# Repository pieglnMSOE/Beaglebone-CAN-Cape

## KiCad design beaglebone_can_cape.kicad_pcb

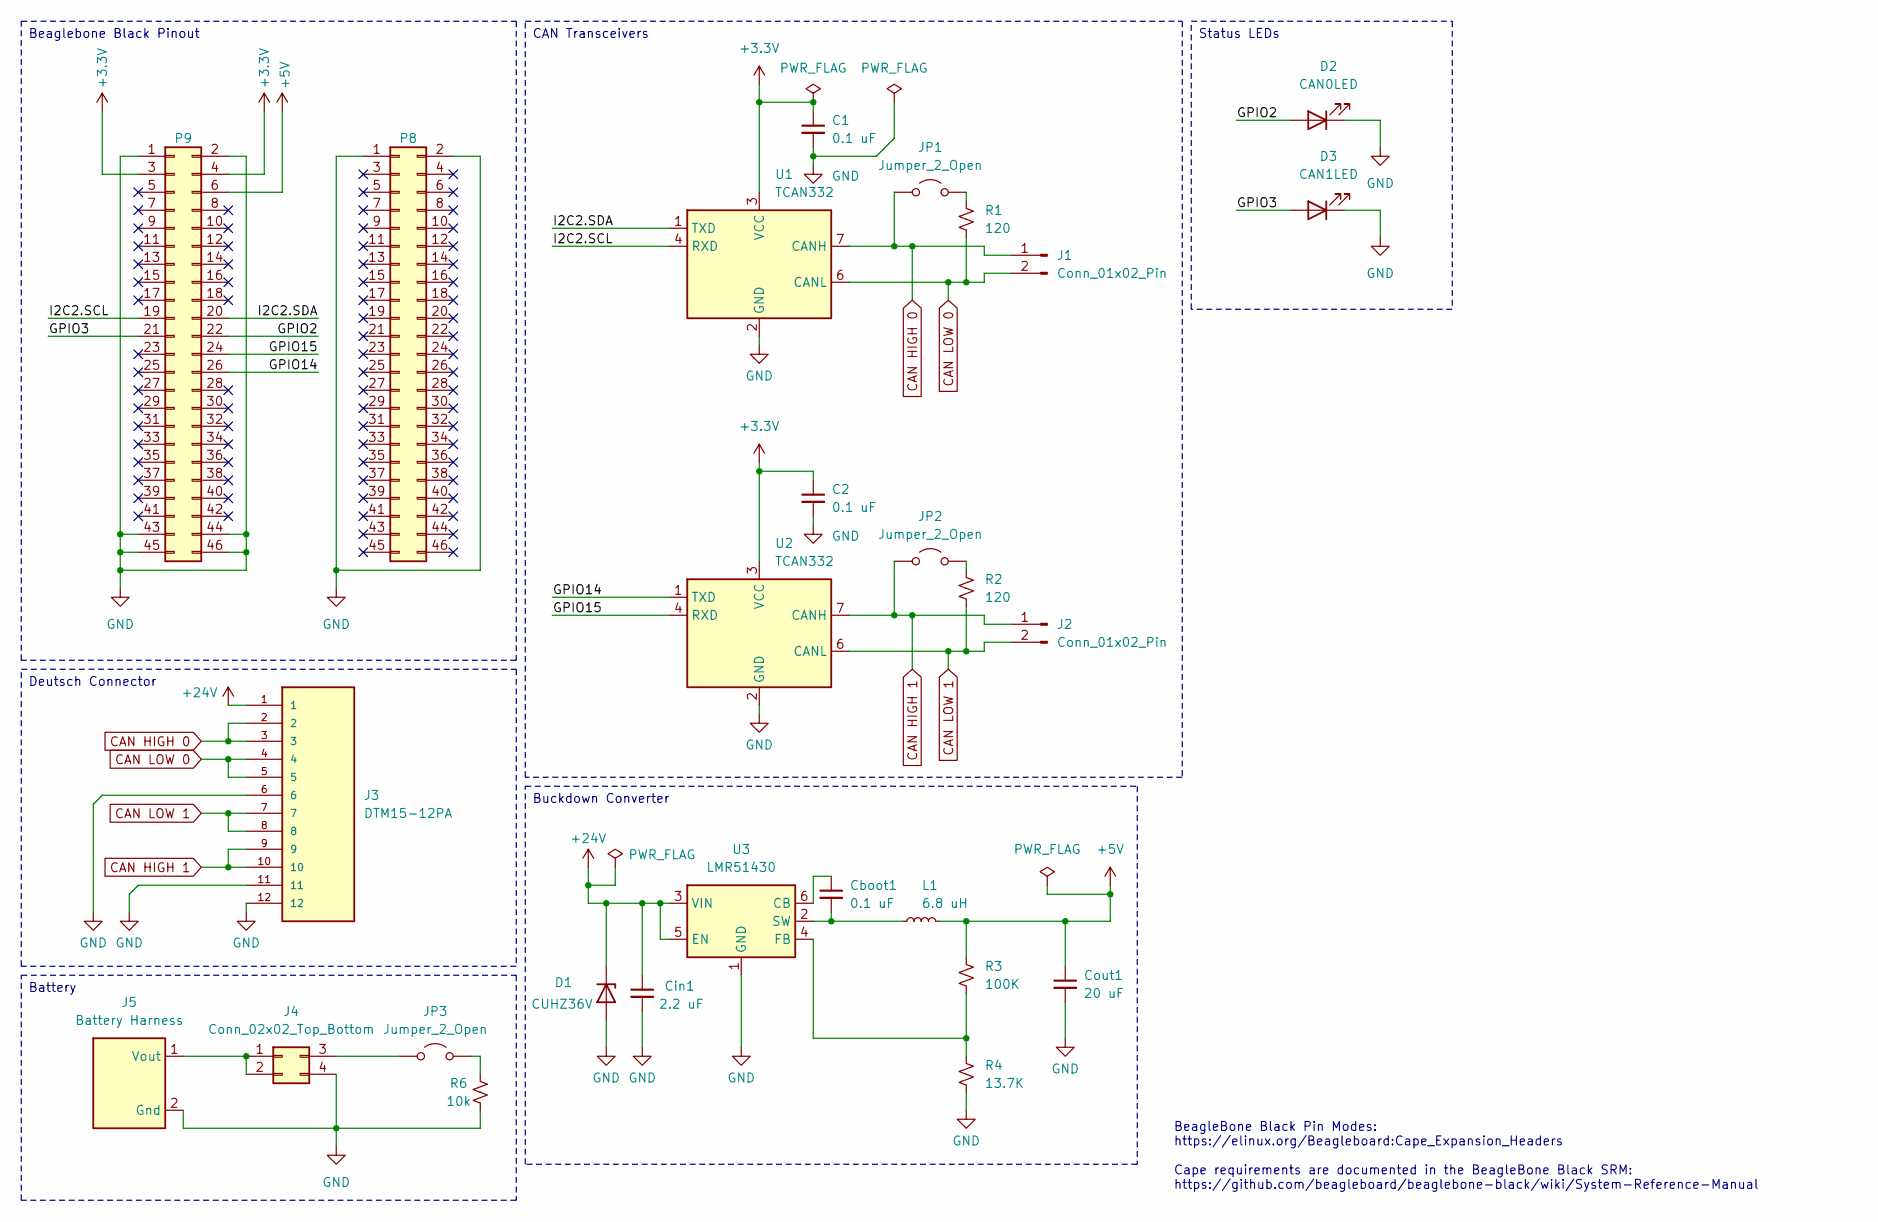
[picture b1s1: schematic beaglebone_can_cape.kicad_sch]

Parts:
C1, C2: 0.1 uF; C_0805_2012Metric
Cboot1: 0.1 uF; C_0805_2012Metric
Cin1: 2.2 uF; CP_Elec_6.3x5.4
Cout1: 20 uF; CP_Elec_6.3x5.4
D1: CUHZ36V; TVSDiode
D2: CAN0LED; LED_0805_2012Metric
D3: CAN1LED; LED_0805_2012Metric
J1, J2: Conn_01x02_Pin; PinHeader_1x02_P2.54mm_Vertical
J3: DTM15-12PA; Deutsch_Marlin; MPN DTM15-12PA
J4: Conn_02x02_Top_Bottom; PinHeader_2x02_P2.54mm_Vertical
J5: Battery Harness; BatteryHolder
JP1, JP2, JP3: Jumper_2_Open; PinHeader_1x02_P2.54mm_Vertical
L1: 6.8 uH; HPC6045NV
P8, P9: BeagleBone_Black_Header; PinHeader_2x23_P2.54mm_Vertical
R1, R2: 120; R_0805_2012Metric
R3: 100K; R_0805_2012Metric
R4: 13.7K; R_0805_2012Metric
R6: 10k; R_0805_2012Metric
U1, U2: TCAN332; D0008A_M
U3: LMR51430; SOT-23-6

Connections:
+3.3V: C1.1, C2.1, P9.3, P9.4, U1.3 (VCC), U2.3 (VCC)
+5V: Cout1.1, L1.2, P9.6, R3.1
+24V: Cin1.1, D1.1 (K), J3.1, U3.3 (VIN), U3.5 (EN)
/GPIO2: D2.2 (A), P9.22
/GPIO3: D3.2 (A), P9.21
/GPIO14: P9.26, U2.1 (TXD)
/GPIO15: P9.24, U2.4 (RXD)
/I2C2.SCL: P9.19, U1.4 (RXD)
/I2C2.SDA: P9.20, U1.1 (TXD)
CAN HIGH 0: J1.1, J3.2, J3.3, JP1.1 (A), U1.7 (CANH)
CAN HIGH 1: J2.1, J3.9, J3.10, JP2.1 (A), U2.7 (CANH)
CAN LOW 0: J1.2, J3.4, J3.5, R1.2, U1.6 (CANL)
CAN LOW 1: J2.2, J3.7, J3.8, R2.2, U2.6 (CANL)
GND: C1.2, C2.2, Cin1.2, Cout1.2, D1.2 (A), D2.1 (K), D3.1 (K), J3.6, J3.11, J3.12, J4.4, J5.2 (Gnd), P8.1, P8.2, P9.1, P9.2, P9.43, P9.44, P9.45, P9.46, R4.2, R6.2, U1.2 (GND), U2.2 (GND), U3.1 (GND)
unnamed: J4.1, J4.2, J5.1 (Vout)
unnamed: J4.3, JP3.1 (A)
unnamed: JP1.2 (B), R1.1
unnamed: JP2.2 (B), R2.1
unnamed: JP3.2 (B), R6.1
unnamed: Cboot1.1, U3.6 (CB)
unnamed: R3.2, R4.1, U3.4 (FB)
unnamed: Cboot1.2, L1.1, U3.2 (SW)

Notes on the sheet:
BeagleBone Black Pin Modes: https://elinux.org/Beagleboard:Cape_Expansion_Headers Cape requirements are documented in the BeagleBone Black SRM: https://github.com/beagleboard/beaglebone-black/wiki/System-Reference-Manual
Deutsch Connector
Beaglebone Black Pinout
Buckdown Converter
Battery
CAN Transceivers
Status LEDs

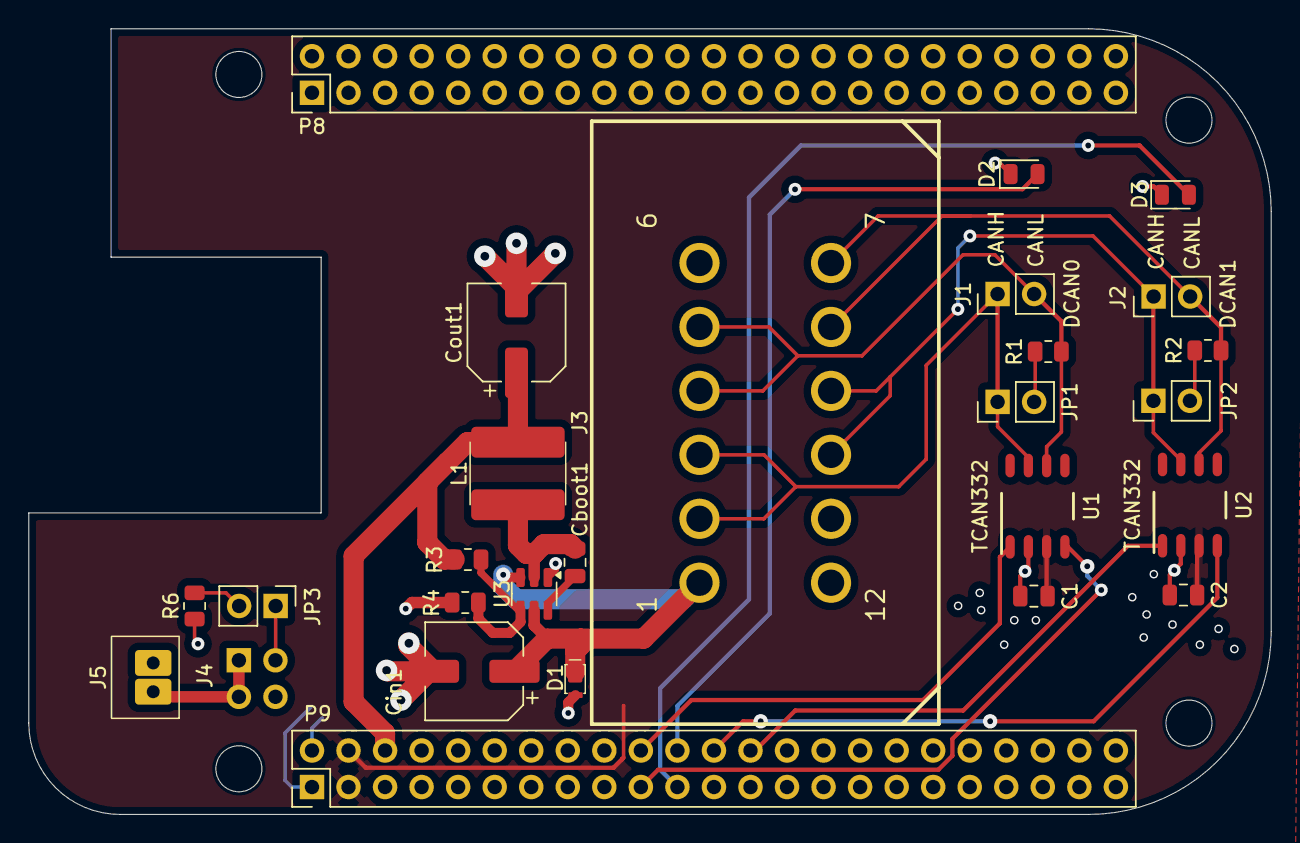
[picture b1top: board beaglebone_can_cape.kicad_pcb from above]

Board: 2 copper layers, 86.4 x 54.6 mm, 31 parts (1 on the bottom side), 22 nets.

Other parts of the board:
MH1, MH2, MH3, MH4: MountingHole_3.2mm_M3_DIN965

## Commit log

2026-01-24 Attempting edits in schematic to push
2026-01-25 Working on schematic file
    added can devices and pinout, needs footprints
2026-02-01 Updating to Zach's
    It works!
2026-02-01 Create .gitignore
    KiCad template awesome
2026-02-02 Finished with schematic
    Did research on TCAN332 vs SN65HVD230, trying TCAN332 first. All footprints loaded.
2026-02-02 Laid out CAN on PCB
    'Nuff said
2026-02-02 Tweaks to footprints
    Moved around pcb silkscreens for readability, think it looks better
2026-02-03 PCB and SCH updates
    Just moved some text boxes, footprints, and explored ideas for the Deutsch connectors.
2026-02-04 Pushing pcb additions of buckdown, need more work on schem
2026-02-04 Removed temp gnd plane b.cu
    nuff said
2026-02-05 Symbol may not be needed, we will see...
2026-02-07 Pushing changes, added deutsch connector and some global variables
2026-02-07 pushing gitignore for my end
2026-02-07 pushing schem from added deutsch
2026-02-08 Schematic + PCB support of Deutsch
    * Imported the DTM15-12PA footprint (this one is not correct as Marlin has a smaller footprint I know now)
    * Removed "PWR" label and replaced with 5V net
    * Reviewed the new schematic fooprint that Zach added, looks good
2026-02-11 taking break, letting Nash cook
2026-02-11 PCB Version 1: Before Week 4 Meeting
    * Reorganized the board to support Deutsch
    * Assigned all components to have footprints
    * Simplified the schematic, namely the pins
    * Created the battery circuit and put on PCB
2026-02-15 did I forget to push this before? oops
2026-02-16 pushing added TVS diode in schem, not wired in yet, working on footprint now
2026-02-16 pushing footprint assignment on schem
2026-02-16 added tvs diode to schem
2026-02-16 pushing for nash work
2026-02-17 Implementing Deutsch + wiring
    * Got rid of more errors and corrected more footprints. Going smoothly.
    * Researched the TVS diode. cool stuff!
2026-02-17 PCB updates
    Wiring and moving TVS and Deutsch
2026-02-17 pushing pwr_flag and ERC changes
2026-02-18 Before-Meeting final PCB and Schematic changes
    * Redid the battery circuit to be... yk... correct because I wired it wrong the first time lols
    * I changed the width of all high voltage & current lines to 0.8mm, really no big change there, nothing had to be moved
    * Looked in depth at anything missing, I think we're just about good to go
2026-02-18 Joey request LED + battery harness things
2026-02-18 pushing changes
2026-02-18 pushing?
2026-02-18 cleaning up
2026-02-18 Touch-ups for PCB + Schematic
    * Made more presentable for tomorrow's advisor meeting
2026-02-18 Cleaned up silkscreen layer
    * Made all descriptors have the same rotation for cleanliness
    * Small bonus, also heavily simplified the battery harness circuit
2026-02-19 crap I didn't pull
2026-02-20 pushing changes complying with 9.4
2026-02-20 pushing one more change
2026-02-20 one more change lol
2026-02-20 Revert "one more change lol"
    This reverts commit 632872a148e7318c24db7e3d55eca11b182aeb42.
2026-02-20 Revert "pushing one more change"
    This reverts commit ff178eb84cf028675ee4f732a8757c322aa0ec1f.
2026-02-20 Revert "pushing changes complying with 9.4"
    This reverts commit c8ddab446e25520ae04b9c74253210672d119c98.
2026-02-20 updated main with 9.4 changes, with battery stuff etc.
2026-02-20 9.4 Changes
    * Checked on the LMR51430 circuit and made R4 + R5 parallel rather than series
    * Electrolytic capacitors needed for Cin and Cout
    * Rewiring of buck down necessary to fit big boy Caps
2026-02-20 pushing changes with big caps
2026-02-20 pushing drc constraint changes
2026-02-21 Beefier TMR Circuit
    * Beefed up the capacitors for the TMR circuit with Zach (earlier today)
    * Begun looking into a beefer inductor (3A min rating w a 5A min SAT current rating) (6060 metrics look good)
    * Added copper floods for thermal relief from inductor to cap and resistor (Vout of TMR)
    * More vias!
2026-02-22 Added new inductor (HPC6045NV) to PCB
    * Finalized PCB with the new inductor gggggggg
2026-02-22 pushing gerbers :D
